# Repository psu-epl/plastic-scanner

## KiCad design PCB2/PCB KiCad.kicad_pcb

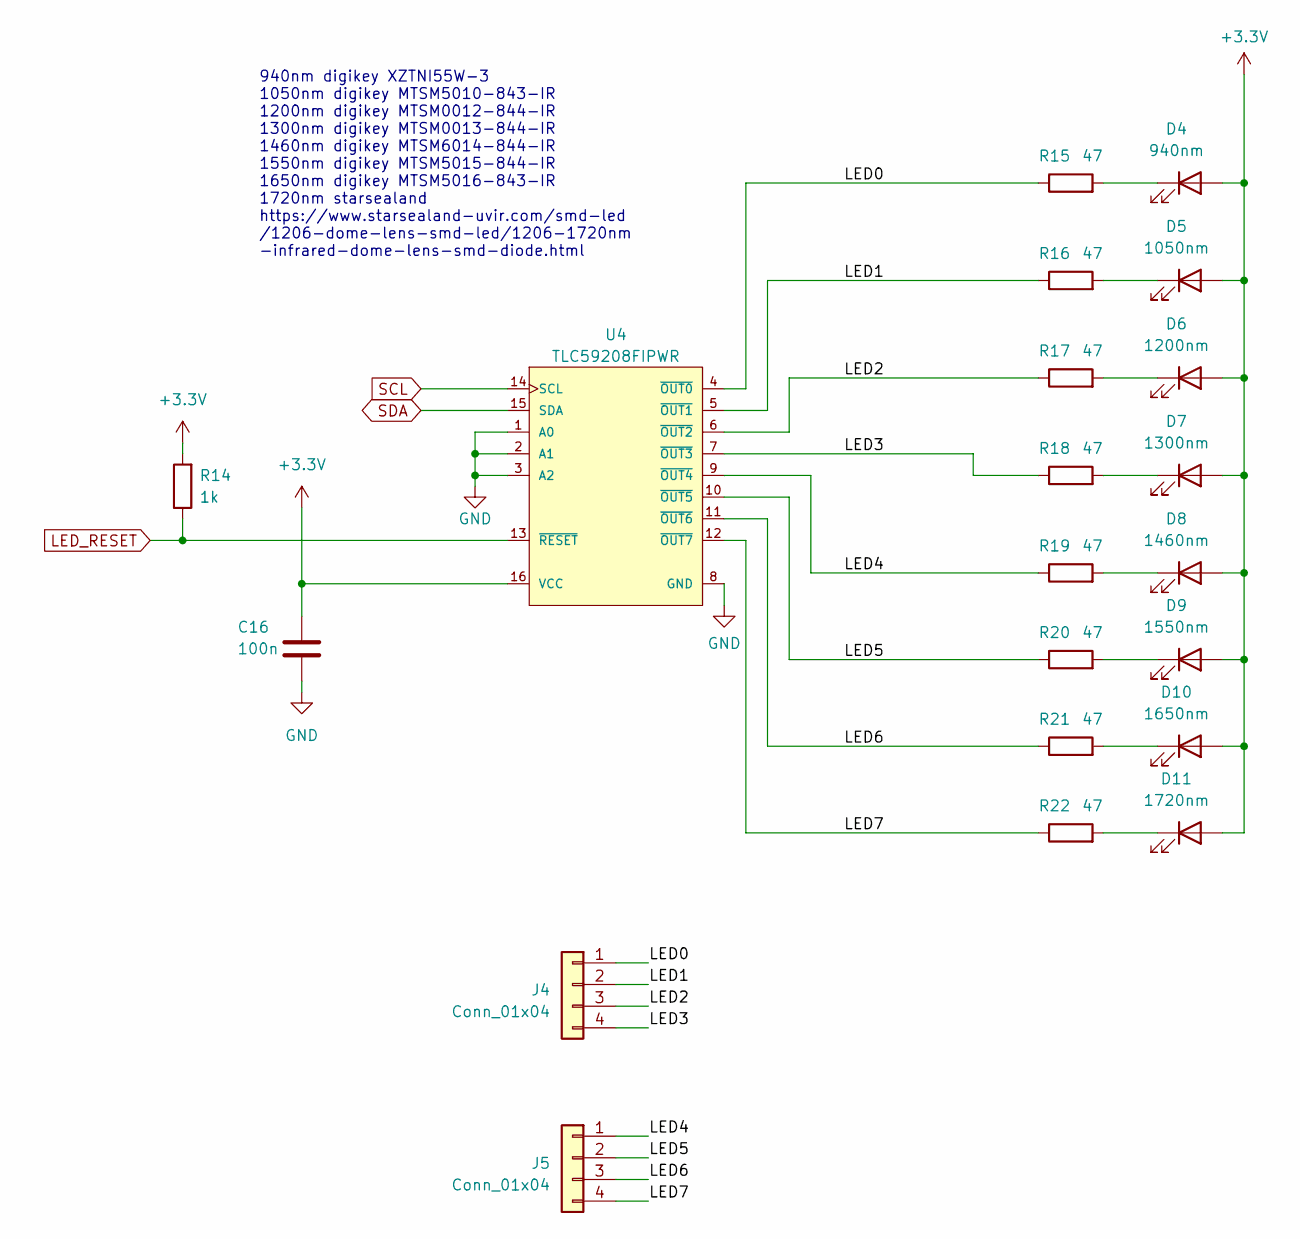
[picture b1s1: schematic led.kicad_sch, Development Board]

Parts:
C16: 100n; C_0805_2012Metric_Pad1.18x1.45mm_HandSolder
D4: 940nm; LED_1206_3216Metric_Pad1.42x1.75mm_HandSolder
D5: 1050nm; LED_1206_3216Metric_Pad1.42x1.75mm_HandSolder
D6: 1200nm; LED_1206_3216Metric_Pad1.42x1.75mm_HandSolder
D7: 1300nm; LED_1206_3216Metric_Pad1.42x1.75mm_HandSolder
D8: 1460nm; LED_1206_3216Metric_Pad1.42x1.75mm_HandSolder
D9: 1550nm; LED_1206_3216Metric_Pad1.42x1.75mm_HandSolder
D10: 1650nm; LED_1206_3216Metric_Pad1.42x1.75mm_HandSolder
D11: 1720nm; LED_1206_3216Metric_Pad1.42x1.75mm_HandSolder
J4, J5: Conn_01x04; PinSocket_1x04_P2.54mm_Vertical
R14: 1k; R_0805_2012Metric_Pad1.20x1.40mm_HandSolder
R15, R16, R17, R18, R19, R20, R21, R22: 47; R_0805_2012Metric_Pad1.20x1.40mm_HandSolder
U4: TLC59208FIPWR; Texas_Instruments-TLC59208FIPWR-Level_A

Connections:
+3.3V: C16.1, D4.2 (A), D5.2 (A), D6.2 (A), D7.2 (A), D8.2 (A), D9.2 (A), D10.2 (A), D11.2 (A), R14.2, U4.16 (VCC); also elsewhere on the board
/LED/LED0: J4.1, R15.1, U4.4 (~OUT0)
/LED/LED1: J4.2, R16.1, U4.5 (~OUT1)
/LED/LED2: J4.3, R17.1, U4.6 (~OUT2)
/LED/LED3: J4.4, R18.1, U4.7 (~OUT3)
/LED/LED4: J5.1, R19.1, U4.9 (~OUT4)
/LED/LED5: J5.2, R20.1, U4.10 (~OUT5)
/LED/LED6: J5.3, R21.1, U4.11 (~OUT6)
/LED/LED7: J5.4, R22.1, U4.12 (~OUT7)
GND: C16.2, U4.1 (A0), U4.2 (A1), U4.3 (A2), U4.8 (GND); also elsewhere on the board
LED_RESET: R14.1, U4.13 (~RESET); also elsewhere on the board
unnamed: D4.1 (K), R15.2
unnamed: D5.1 (K), R16.2
unnamed: D6.1 (K), R17.2
unnamed: D7.1 (K), R18.2
unnamed: D8.1 (K), R19.2
unnamed: D9.1 (K), R20.2
unnamed: D10.1 (K), R21.2
unnamed: D11.1 (K), R22.2
SCL: U4.14 (SCL); also elsewhere on the board
SDA: U4.15 (SDA); also elsewhere on the board

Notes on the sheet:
940nm digikey XZTNI55W-3 1050nm digikey MTSM5010-843-IR 1200nm digikey MTSM0012-844-IR 1300nm digikey MTSM0013-844-IR 1460nm digikey MTSM6014-844-IR 1550nm digikey MTSM5015-844-IR 1650nm digikey MTSM5016-843-IR 1720nm starsealand https://www.starsealand-uvir.com/smd-led /1206-dome-lens-smd-led/1206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

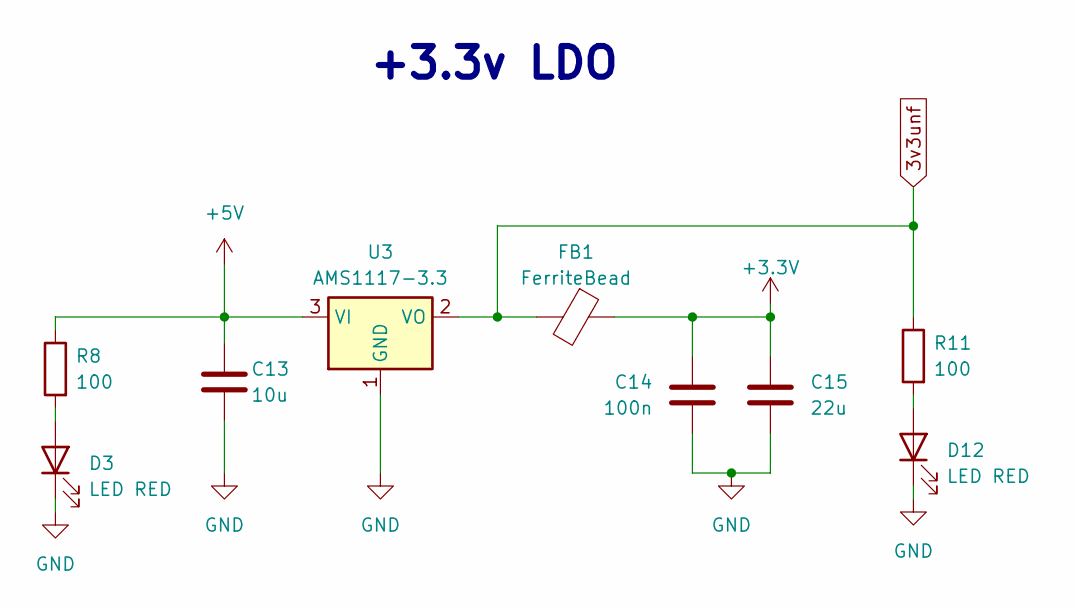
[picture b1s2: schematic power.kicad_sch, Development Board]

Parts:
C13: 10u; C_0805_2012Metric_Pad1.18x1.45mm_HandSolder
C14: 100n; C_0805_2012Metric_Pad1.18x1.45mm_HandSolder
C15: 22u; C_0805_2012Metric_Pad1.18x1.45mm_HandSolder
D3, D12: LED RED; LED_0805_2012Metric_Pad1.15x1.40mm_HandSolder
FB1: FerriteBead; R_0805_2012Metric_Pad1.20x1.40mm_HandSolder
R8, R11: 100; R_0805_2012Metric_Pad1.20x1.40mm_HandSolder
U3: AMS1117-3.3; SOT-223-3_TabPin2

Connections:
3v3unf: FB1.2, R11.1, U3.2 (VO); also elsewhere on the board
+3.3V: C14.2, C15.1, FB1.1; also elsewhere on the board
+5V: C13.1, R8.1, U3.3 (VI); also elsewhere on the board
GND: C13.2, C14.1, C15.2, D3.1 (K), D12.1 (K), U3.1 (GND); also elsewhere on the board
unnamed: D3.2 (A), R8.2
unnamed: D12.2 (A), R11.2

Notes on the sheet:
+3.3v LDO

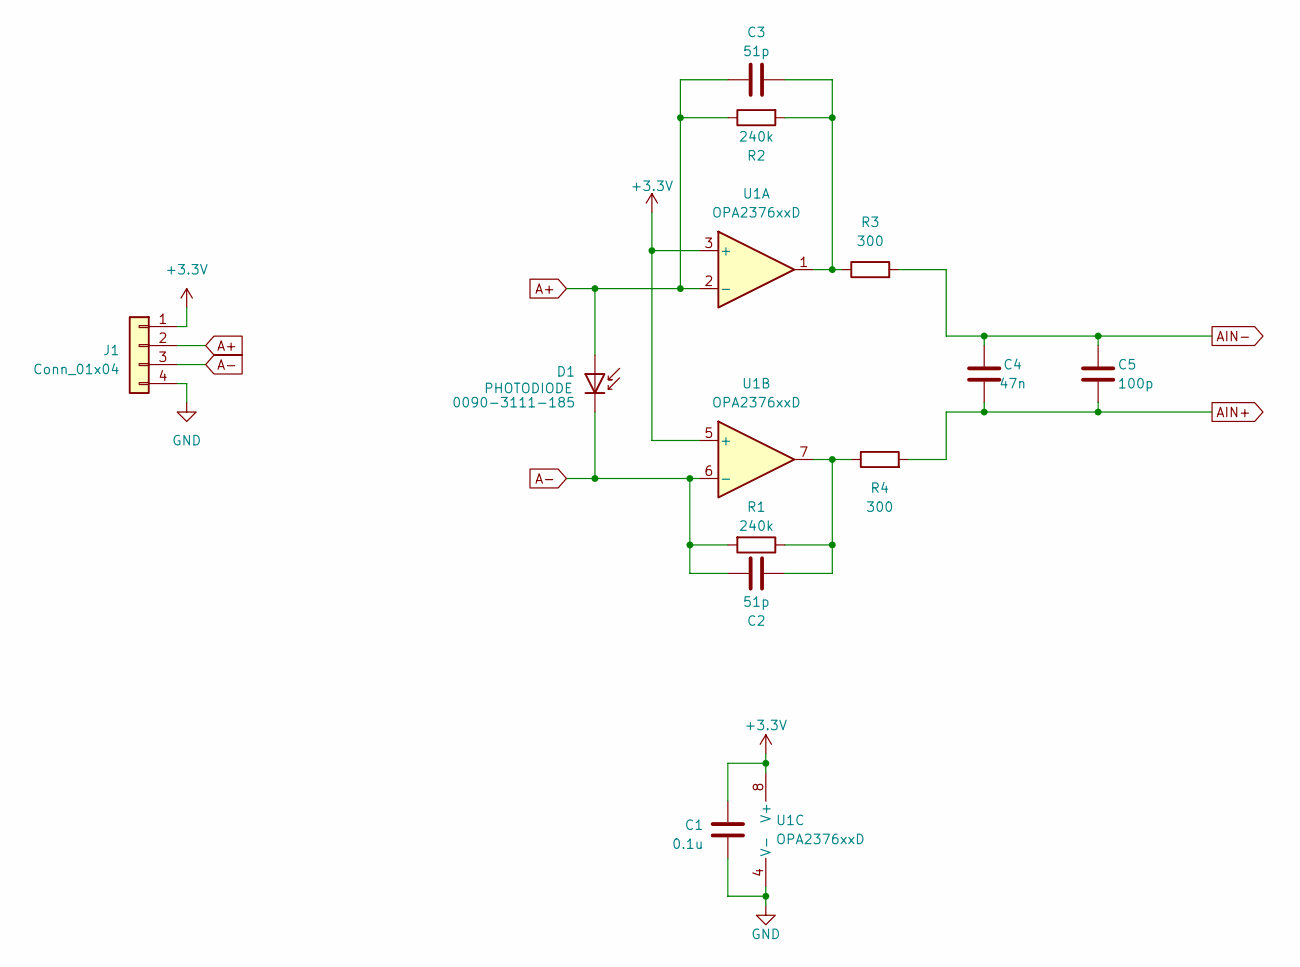
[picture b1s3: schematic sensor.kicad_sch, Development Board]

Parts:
C1: 0.1u; C_0805_2012Metric_Pad1.18x1.45mm_HandSolder
C2, C3: 51p; C_0805_2012Metric_Pad1.18x1.45mm_HandSolder
C4: 47n; C_0805_2012Metric_Pad1.18x1.45mm_HandSolder
C5: 100p; C_0805_2012Metric_Pad1.18x1.45mm_HandSolder
D1: 0090-3111-185; D_1206_3216Metric_Pad1.42x1.75mm_HandSolder
J1: Conn_01x04; PinSocket_1x04_P2.54mm_Vertical
R1, R2: 240k; R_0805_2012Metric_Pad1.20x1.40mm_HandSolder
R3, R4: 300; R_0805_2012Metric_Pad1.20x1.40mm_HandSolder
U1: OPA2376xxD; SOIC127P599X175-8N

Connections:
+3.3V: C1.2, J1.1, U1.3 (+), U1.5 (+), U1.8 (V+); also elsewhere on the board
A+: C3.1, D1.2 (A), J1.2, R2.1, U1.2 (-)
A-: C2.1, D1.1 (K), J1.3, R1.2, U1.6 (-)
AIN+: C4.1, C5.2, R4.2; also elsewhere on the board
AIN-: C4.2, C5.1, R3.2; also elsewhere on the board
GND: C1.1, J1.4, U1.4 (V-); also elsewhere on the board
unnamed: C2.2, R1.1, R4.1, U1.7
unnamed: C3.2, R2.2, R3.1, U1.1

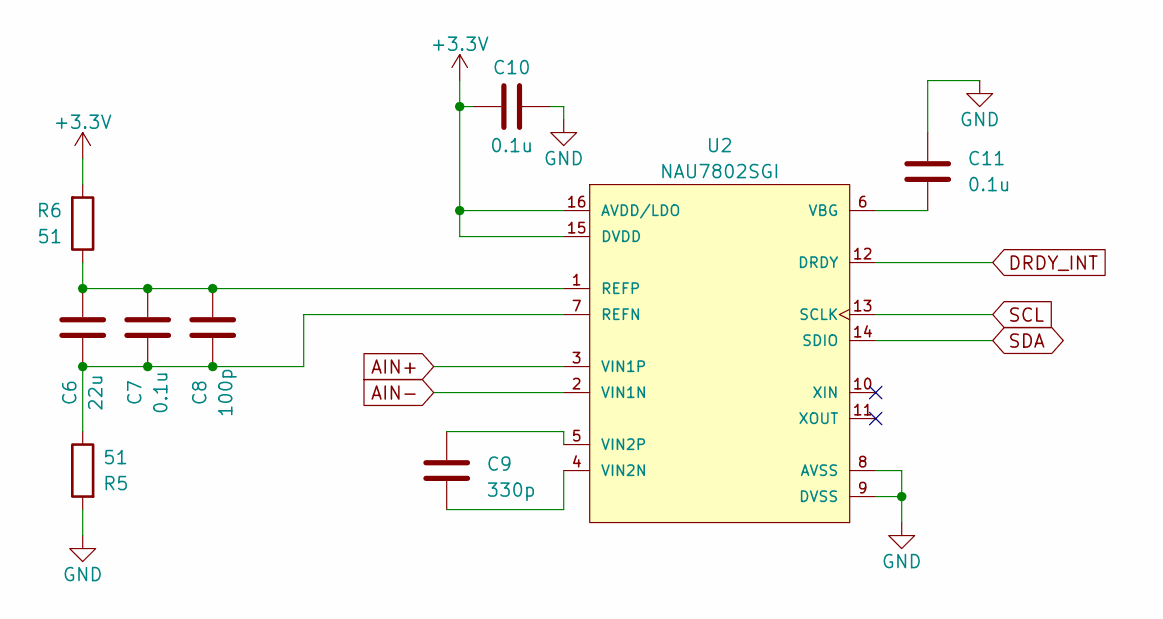
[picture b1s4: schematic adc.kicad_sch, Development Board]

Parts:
C6: 22u; C_0805_2012Metric_Pad1.18x1.45mm_HandSolder
C7, C10, C11: 0.1u; C_0805_2012Metric_Pad1.18x1.45mm_HandSolder
C8: 100p; C_0805_2012Metric_Pad1.18x1.45mm_HandSolder
C9: 330p; C_0805_2012Metric_Pad1.18x1.45mm_HandSolder
R5, R6: 51; R_0805_2012Metric_Pad1.20x1.40mm_HandSolder
U2: NAU7802SGI; Nuvoton-NAU7802SGI-0-0-0; digikey description IC ADC 24BIT I2C/SRL 16-SOP

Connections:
+3.3V: C10.1, R6.2, U2.15 (DVDD), U2.16 (AVDD/LDO); also elsewhere on the board
AIN+: U2.3 (VIN1P); also elsewhere on the board
AIN-: U2.2 (VIN1N); also elsewhere on the board
DRDY_INT: U2.12 (DRDY); also elsewhere on the board
GND: C10.2, C11.1, R5.2, U2.8 (AVSS), U2.9 (DVSS); also elsewhere on the board
unnamed: C6.1, C7.1, C8.1, R5.1, U2.7 (REFN)
unnamed: C6.2, C7.2, C8.2, R6.1, U2.1 (REFP)
unnamed: C11.2, U2.6 (VBG)
unnamed: C9.2, U2.4 (VIN2N)
unnamed: C9.1, U2.5 (VIN2P)
SCL: U2.13 (SCLK); also elsewhere on the board
SDA: U2.14 (SDIO); also elsewhere on the board

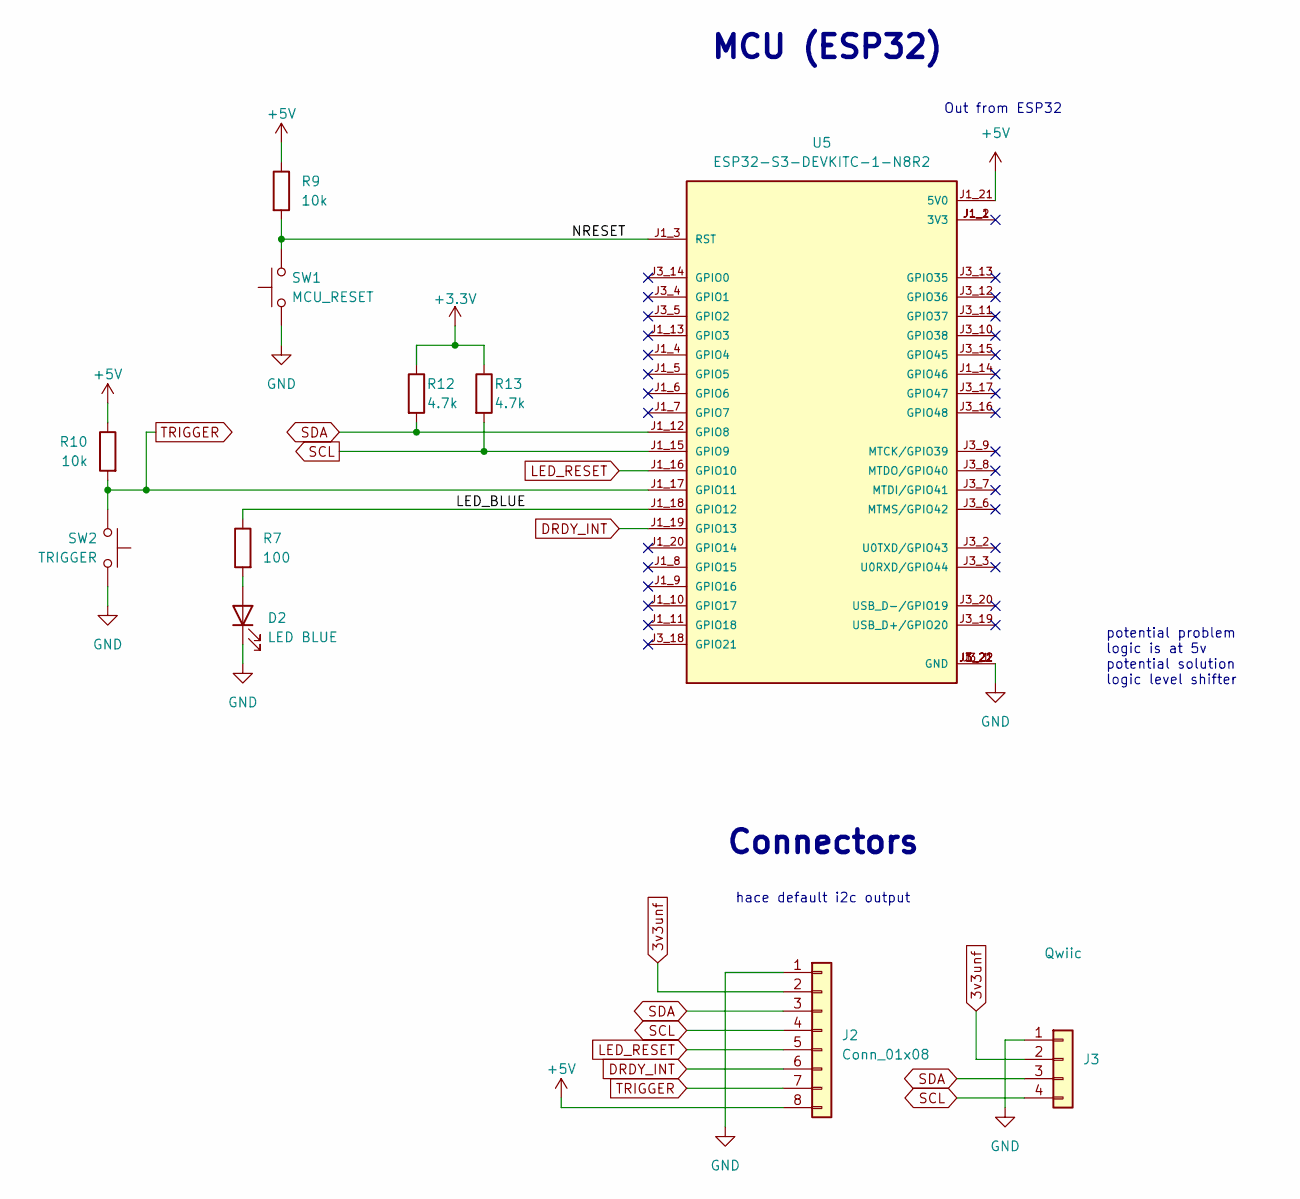
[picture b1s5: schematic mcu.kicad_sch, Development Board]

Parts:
D2: LED BLUE; LED_0805_2012Metric_Pad1.15x1.40mm_HandSolder
J2: Conn_01x08; PinHeader_1x08_P2.54mm_Vertical
J3: Qwiic; JST_SH_SM04B-SRSS-TB_1x04-1MP_P1.00mm_Horizontal
R7: 100; R_0805_2012Metric_Pad1.20x1.40mm_HandSolder
R9, R10: 10k; R_0805_2012Metric_Pad1.20x1.40mm_HandSolder
R12, R13: 4.7k; R_0805_2012Metric_Pad1.20x1.40mm_HandSolder
SW1: MCU_RESET; SW_PUSH_6mm
SW2: TRIGGER; SW_PUSH_6mm
U5: ESP32-S3-DEVKITC-1-N8R2; XCVR_ESP32-S3-DEVKITC-1-N8R2; PARTREV V1

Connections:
3v3unf: J2.2, J3.2; also elsewhere on the board
+3.3V: R12.1, R13.1; also elsewhere on the board
+5V: J2.8, R9.1, R10.1, U5.J1_21 (5V0); also elsewhere on the board
/MCU + IO/LED_BLUE: R7.1, U5.J1_18 (GPIO12)
/MCU + IO/NRESET: R9.2, SW1.2, U5.J1_3 (RST)
DRDY_INT: J2.6, U5.J1_19 (GPIO13); also elsewhere on the board
GND: D2.1 (K), J2.1, J3.1, SW1.1, SW2.1, U5.J1_22 (GND), U5.J3_1 (GND), U5.J3_21 (GND), U5.J3_22 (GND); also elsewhere on the board
LED_RESET: J2.5, U5.J1_16 (GPIO10); also elsewhere on the board
unnamed: D2.2 (A), R7.2
SCL: J2.4, J3.4, R13.2, U5.J1_15 (GPIO9); also elsewhere on the board
SDA: J2.3, J3.3, R12.2, U5.J1_12 (GPIO8); also elsewhere on the board
TRIGGER: J2.7, R10.2, SW2.2, U5.J1_17 (GPIO11)

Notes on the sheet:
MCU (ESP32)
potential problem logic is at 5v potential solution logic level shifter
Out from ESP32
hace default i2c output
Connectors

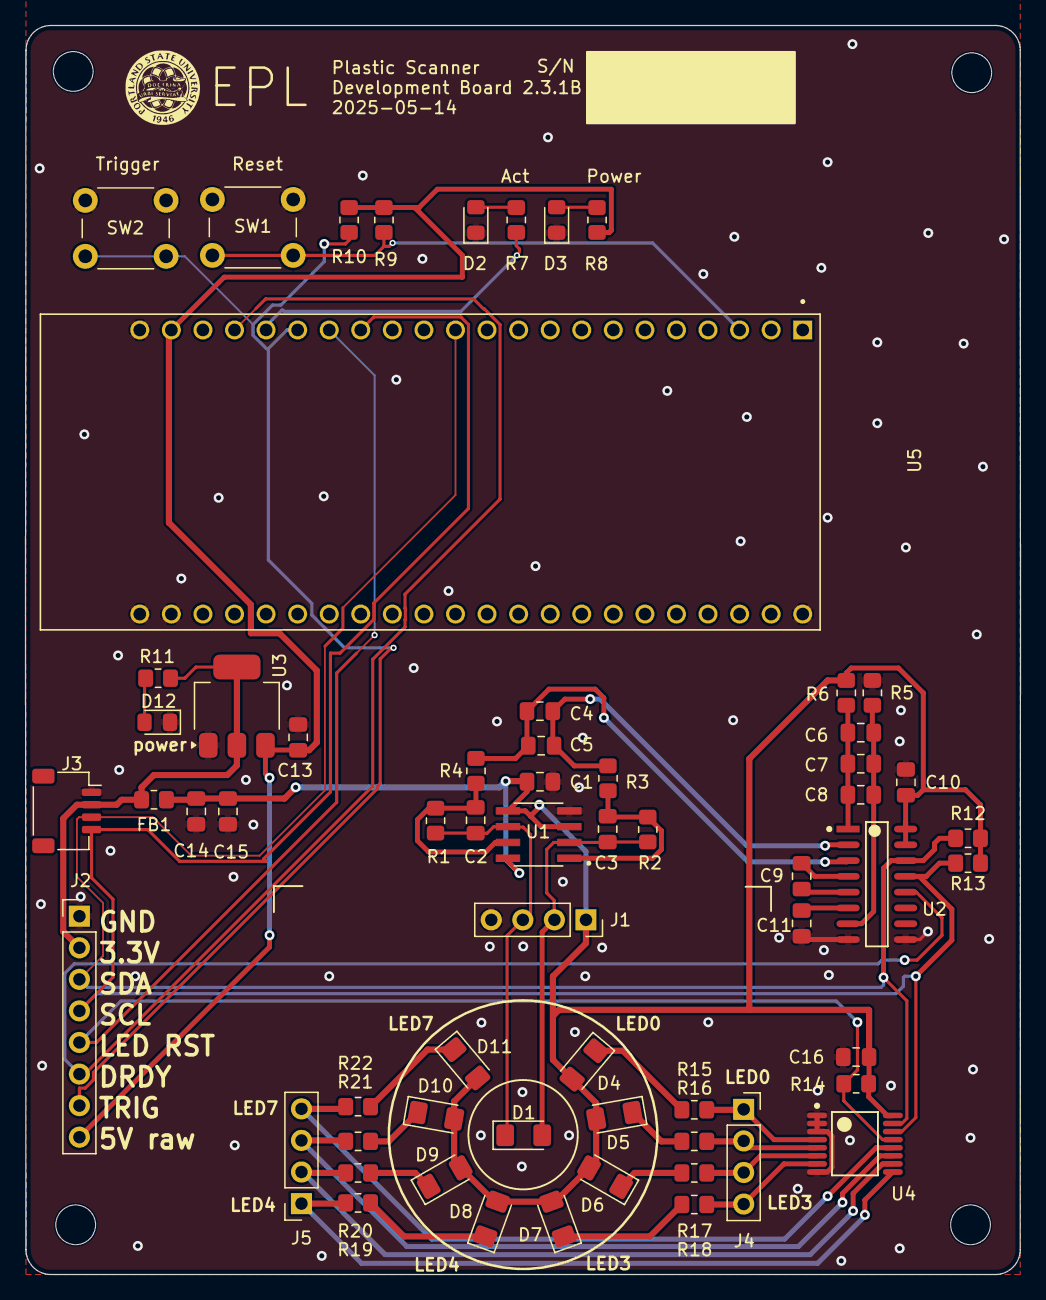
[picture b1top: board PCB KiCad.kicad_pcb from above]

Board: 2 copper layers, 80.1 x 100.5 mm, 64 parts (1 on the bottom side), 41 nets.

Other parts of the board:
G1: LOGO
e: MountingHole_3.2mm_M3

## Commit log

2025-03-27 Minor schematic cleanup!
2025-03-27 Giant schematic cleanup to make more sense of the sensor circuit and just clean everything up a bit.
2025-03-27 Relabel LEDs 0 - 7 and put that on the silkscreen for reference.
2025-04-30 Create Wifi_test
2025-04-30 Create Test
2025-05-15 PCB version 2 with wifi
2025-05-15 wifi test code clean up
2025-05-15 moved to firmware github
2025-05-15 ESP32 footprint
2025-05-15 Better .gitignore
2025-05-15 Removed temporary files
2025-05-15 fixed erc errors added library to path
2025-05-15 updated pcb traces
2025-05-23 added a github barcode and gerbers files in pcb2 folder
